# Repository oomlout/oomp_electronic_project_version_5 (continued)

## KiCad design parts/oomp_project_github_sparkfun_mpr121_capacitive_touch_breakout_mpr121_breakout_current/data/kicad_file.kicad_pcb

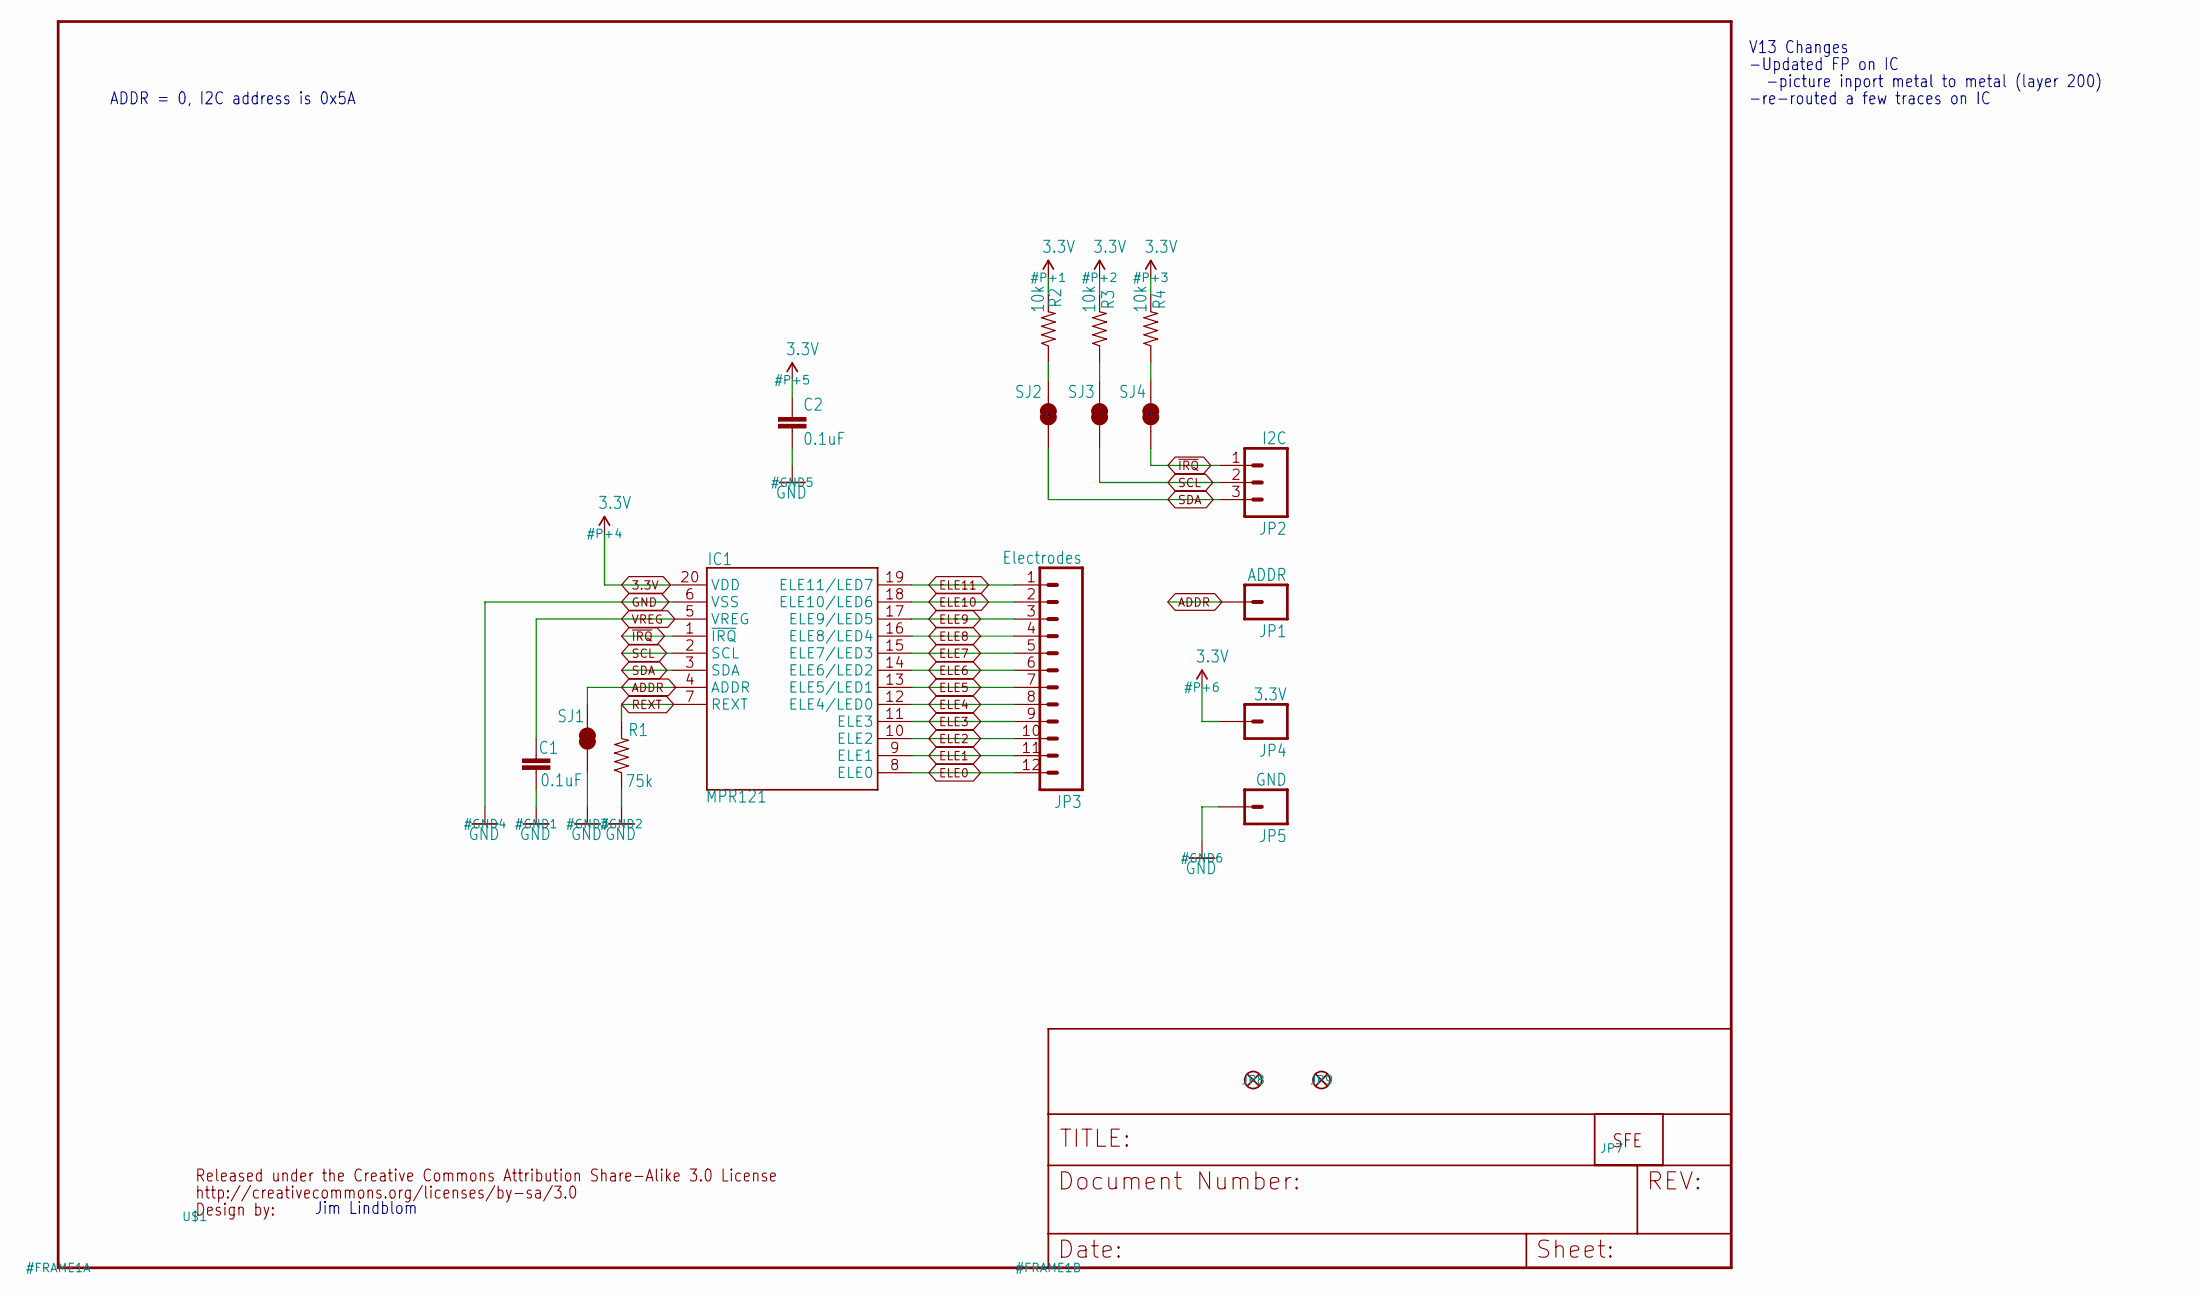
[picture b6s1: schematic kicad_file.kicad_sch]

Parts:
C1, C2: 0.1uF; 0603-CAP
IC1: MPR121; QFN-20-0.4MM-V2
JP1: ADDR; 1X01
JP2: I2C; 1X03
JP3: Electrodes; 1X12
JP4: 3.3V; 1X01
JP5: GND; 1X01
JP7: LOGO-SFENEW; SFE-NEW-WEBLOGO
JP8, JP9: FIDUCIAL1X2; FIDUCIAL-1X2
R1: 75k; 0603-RES
R2, R3, R4: 10k; 0603-RES
SJ1, SJ2, SJ3, SJ4: SOLDERJUMPERTRACE; SJ_2S-TRACE
U$1: CREATIVE_COMMONS

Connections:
3.3V: C2.1, IC1.20 (VDD), JP4.1, R2.2, R3.2, R4.2
ADDR: IC1.4 (ADDR), JP1.1, SJ1.2
ELE0: IC1.8 (ELE0), JP3.12
ELE1: IC1.9 (ELE1), JP3.11
ELE2: IC1.10 (ELE2), JP3.10
ELE3: IC1.11 (ELE3), JP3.9
ELE4: IC1.12 (ELE4/LED0), JP3.8
ELE5: IC1.13 (ELE5/LED1), JP3.7
ELE6: IC1.14 (ELE6/LED2), JP3.6
ELE7: IC1.15 (ELE7/LED3), JP3.5
ELE8: IC1.16 (ELE8/LED4), JP3.4
ELE9: IC1.17 (ELE9/LED5), JP3.3
ELE10: IC1.18 (ELE10/LED6), JP3.2
ELE11: IC1.19 (ELE11/LED7), JP3.1
GND: C1.2, C2.2, IC1.6 (VSS), JP5.1, R1.1, SJ1.1
REXT: IC1.7 (REXT), R1.2
SCL: IC1.2 (SCL), JP2.2, SJ3.1
SCL_PU: R3.1, SJ3.2
SDA: IC1.3 (SDA), JP2.3, SJ2.1
SDA_PU: R2.1, SJ2.2
VREG: C1.1, IC1.5 (VREG)
~IRQ_PU: R4.1, SJ4.2
~IRQ: IC1.1 (~IRQ), JP2.1, SJ4.1

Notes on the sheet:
-re-routed a few traces on IC
V13 Changes
Jim Lindblom
-Updated FP on IC
-picture inport metal to metal (layer 200)
ADDR = 0, I2C address is 0x5A

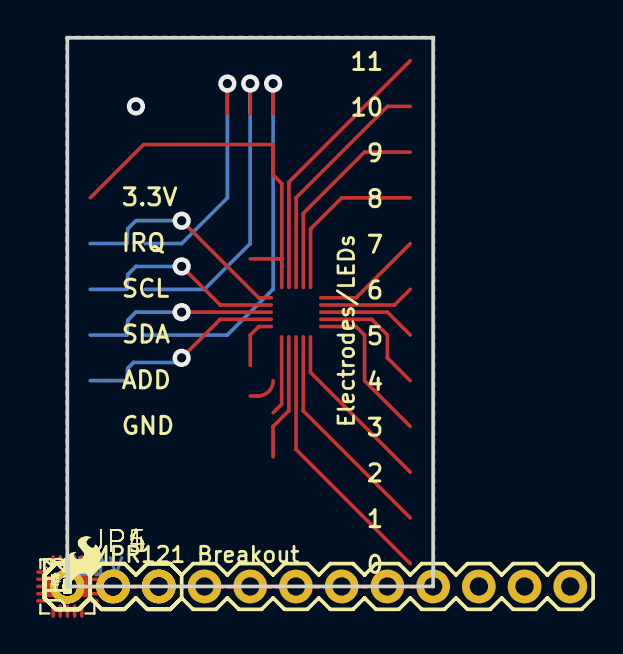
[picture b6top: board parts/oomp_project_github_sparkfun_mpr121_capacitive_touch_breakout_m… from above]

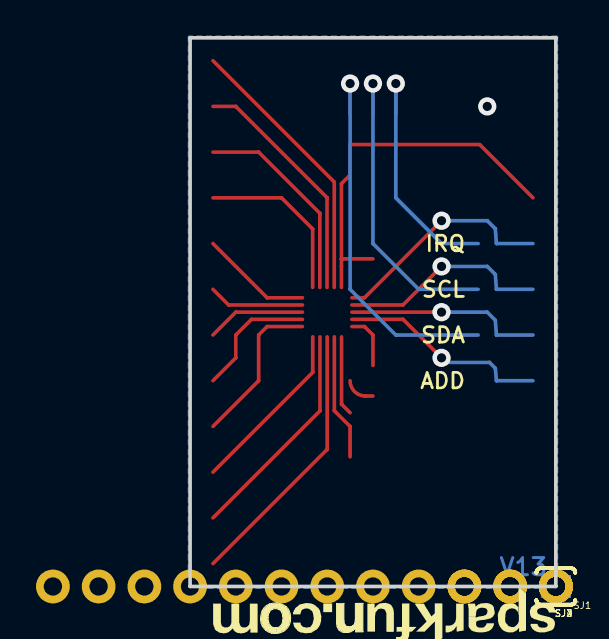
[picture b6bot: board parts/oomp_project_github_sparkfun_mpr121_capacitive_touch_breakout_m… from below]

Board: 2 copper layers, 20.3 x 30.5 mm, 21 parts (5 on the bottom side), 23 nets.

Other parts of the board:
JP6: LOGO-SFESK; SFE-LOGO-FLAME

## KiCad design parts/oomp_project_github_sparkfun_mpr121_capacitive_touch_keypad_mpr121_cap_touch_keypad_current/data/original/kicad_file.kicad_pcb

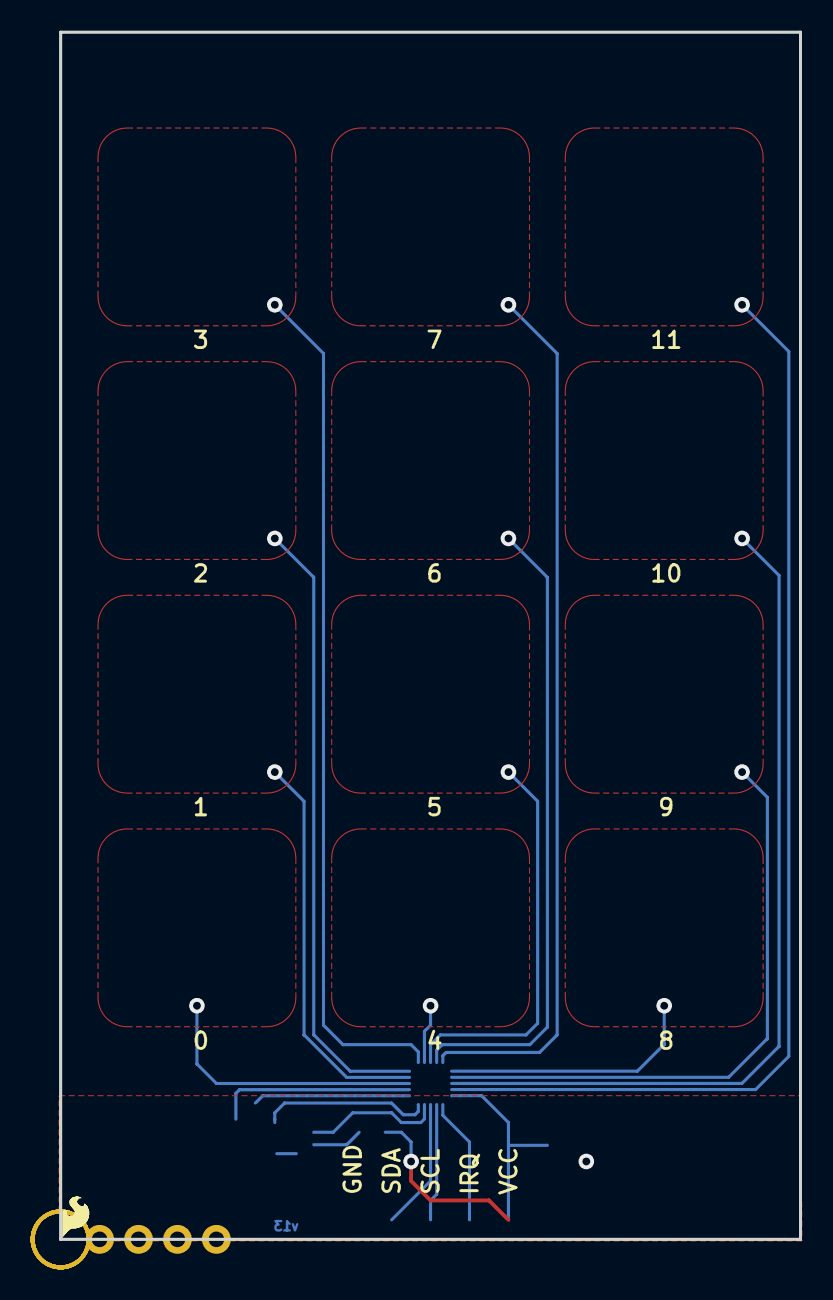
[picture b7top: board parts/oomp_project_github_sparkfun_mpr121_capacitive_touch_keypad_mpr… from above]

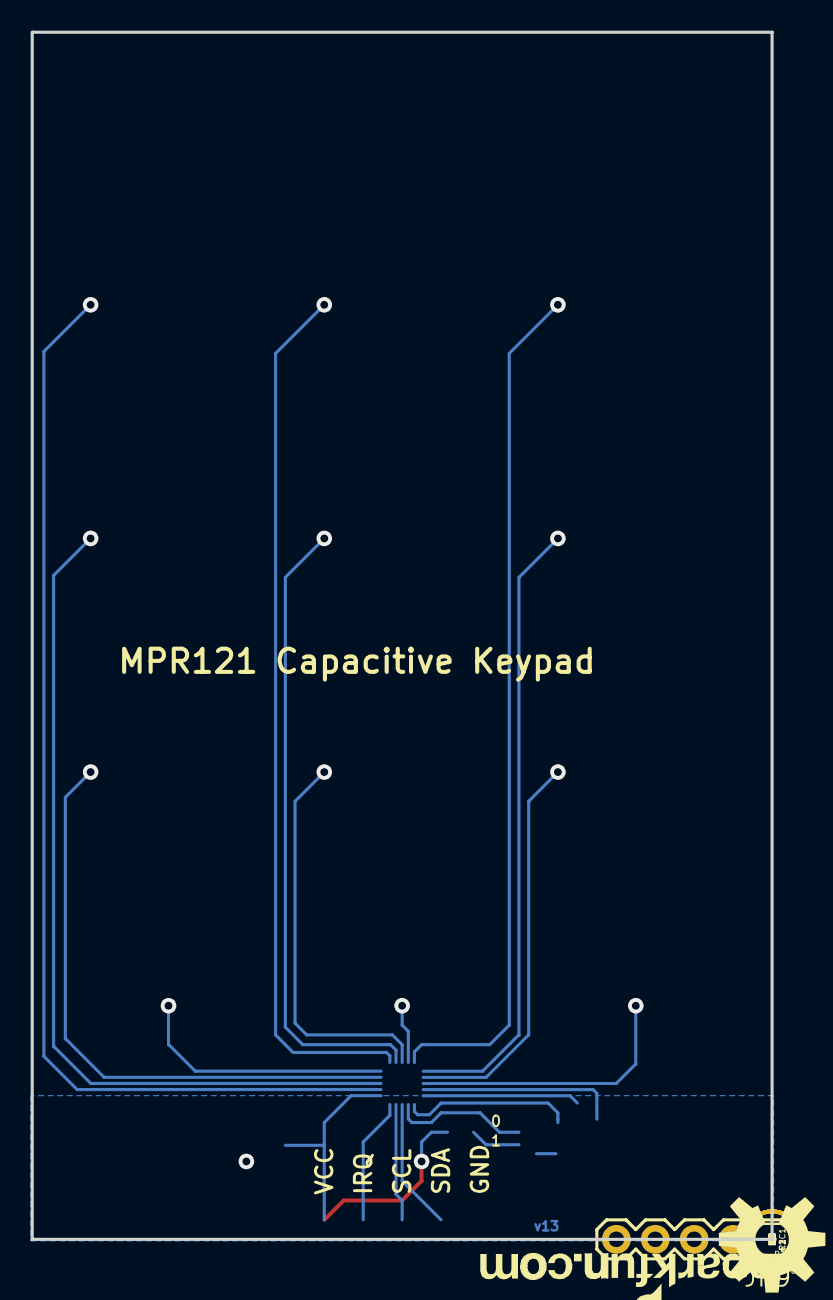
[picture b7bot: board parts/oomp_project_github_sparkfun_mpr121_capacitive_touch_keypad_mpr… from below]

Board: 2 copper layers, 48.3 x 78.7 mm, 19 parts (15 on the bottom side), 9 nets.

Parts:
C1, C2: 0.1uF; 0603-CAP
FRAME1: FRAME-LETTER; CREATIVE_COMMONS
IC1: MPR121; QFN-20-0.4MM-V2
JP1: LOGO-SFENEW; SFE-NEW-WEBLOGO
JP2, JP6: LOGO-SFESK; SFE-LOGO-FLAME
JP3, JP4, JP7, JP8: STAND-OFF
JP5, JP10: FIDUCIAL1X2; FIDUCIAL-1X2
JP9: 1X05
LOGO1: OSHW-LOGOL; OSHW-LOGO-L
R1: 75k; 0603-RES
R2: 10K; 0603-RES
SJ1: SJ_3_PASTE1&2
U$1: REVISION

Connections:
GND: C1.2, C2.2, IC1.6, JP9.1, R1.1, SJ1.1
unnamed: IC1.4, SJ1.2
unnamed: R2.1, SJ1.3
REXT: IC1.7, R1.2
SCL: IC1.2, JP9.3
SDA: IC1.3, JP9.2
VCC: C2.1, IC1.20, JP9.5, R2.2
VREG: C1.1, IC1.5
~IRQ: IC1.1, JP9.4

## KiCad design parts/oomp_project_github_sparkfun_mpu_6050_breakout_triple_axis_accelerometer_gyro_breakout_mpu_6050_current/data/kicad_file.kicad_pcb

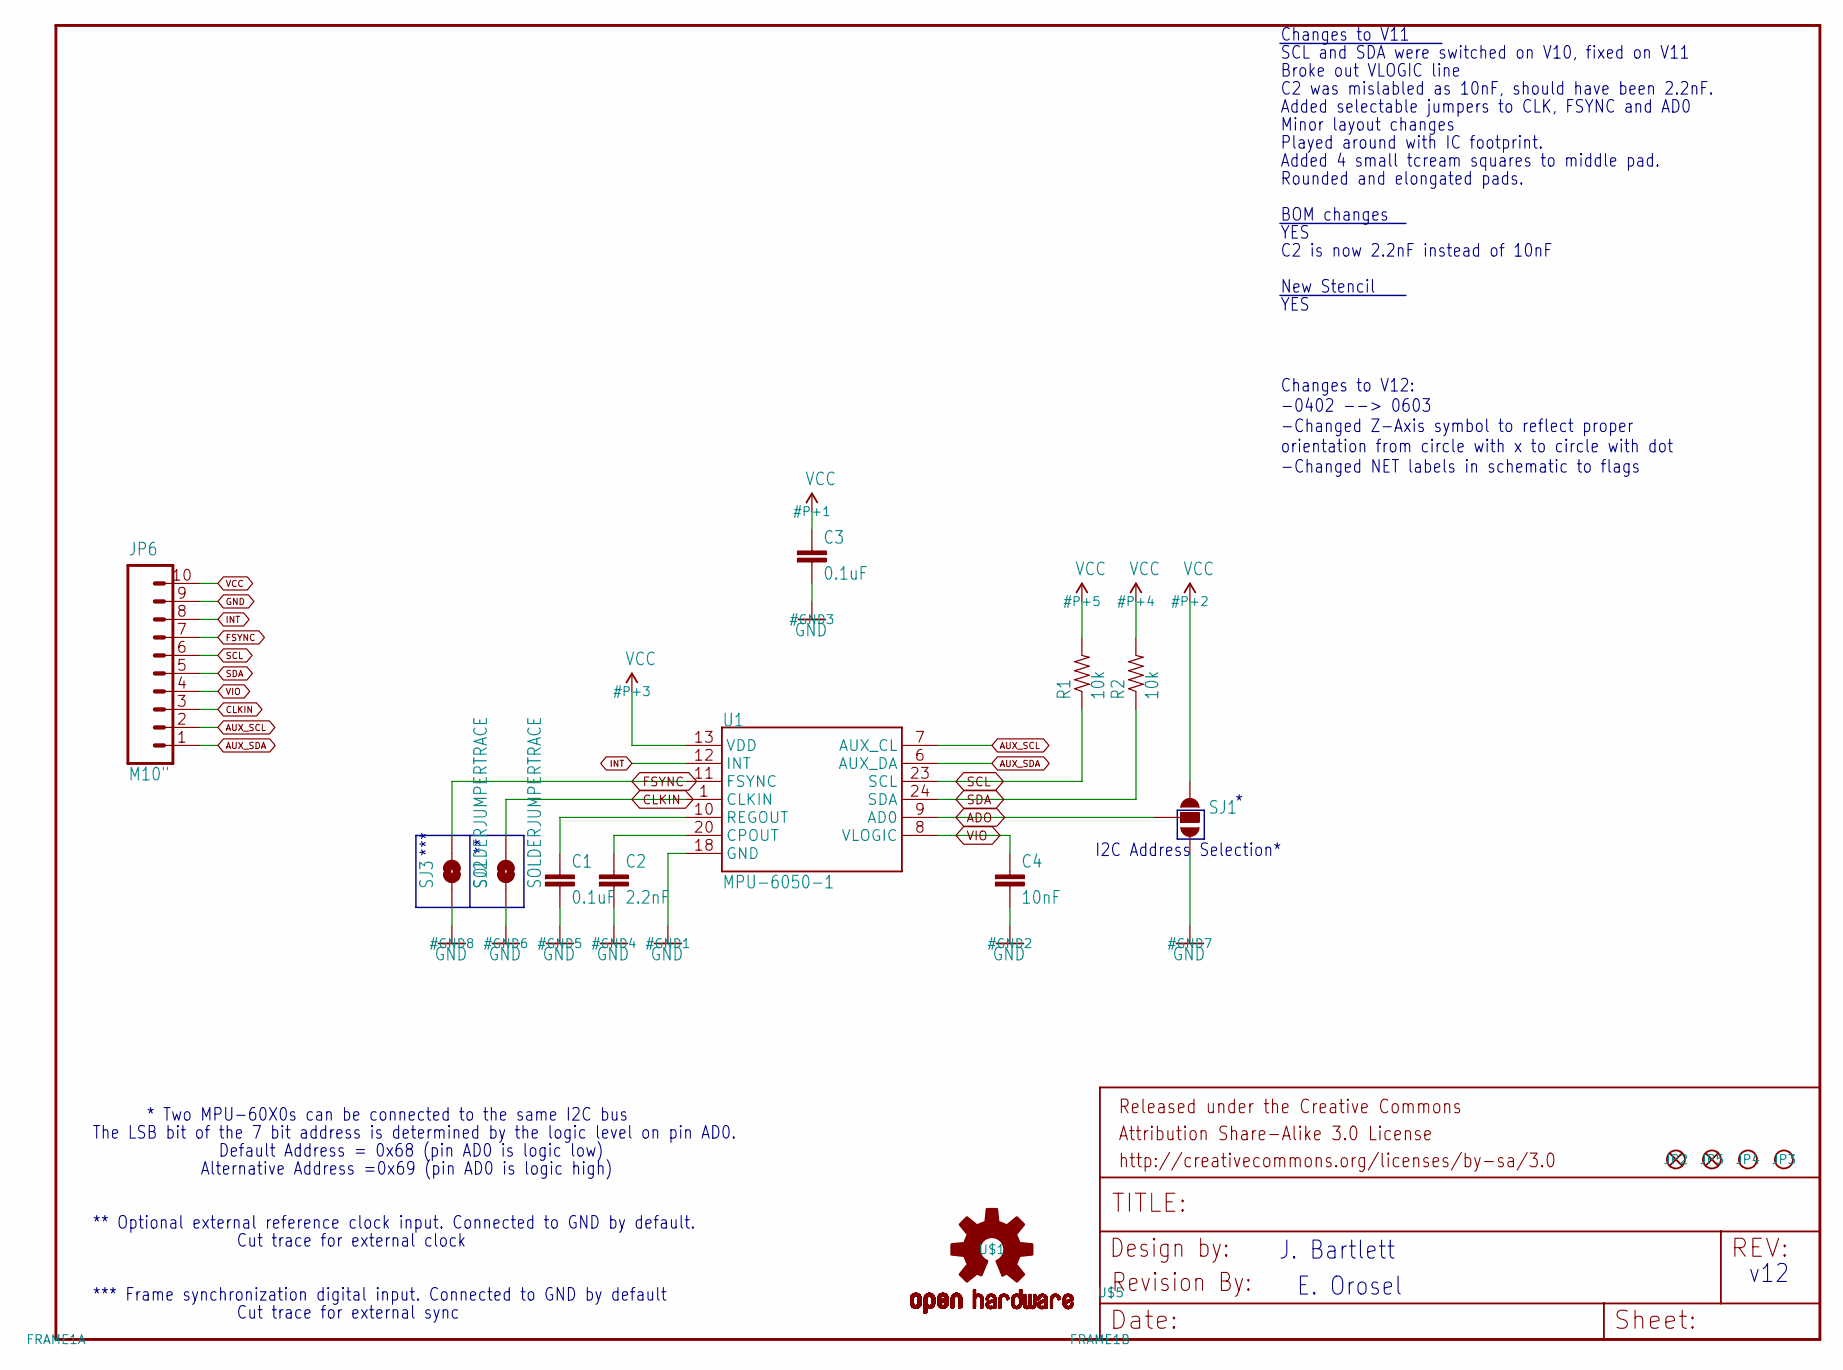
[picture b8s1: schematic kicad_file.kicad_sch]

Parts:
C1, C3: 0.1uF; 0603-CAP
C2: 2.2nF; 0603-CAP
C4: 10nF; 0603-CAP
FRAME1: FRAME-LETTER; CREATIVE_COMMONS
JP2, JP5: FIDUCIALUFIDUCIAL; MICRO-FIDUCIAL
JP3, JP4: STAND-OFFTIGHT; STAND-OFF-TIGHT
JP6: M10"; 1X10
R1, R2: 10k; 0603-RES
SJ1: SOLDERJUMPER_2WAYPASTE2&3; SJ_3_PASTE2&3
SJ2, SJ3: SOLDERJUMPERTRACE; SJ_2S-TRACE
U1: MPU-6050-1; QFN-24-4MM2
U$1: OSHW-LOGOS; OSHW-LOGO-S
U$5: REVISION

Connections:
ADO: SJ1.2, U1.9 (AD0)
AUX_SCL: JP6.2, U1.7 (AUX_CL)
AUX_SDA: JP6.1, U1.6 (AUX_DA)
CLKIN: JP6.3, SJ2.2, U1.1 (CLKIN)
FSYNC: JP6.7, SJ3.2, U1.11 (FSYNC)
GND: C1.2, C2.2, C3.2, C4.2, JP6.9, SJ1.3, SJ2.1, SJ3.1, U1.18 (GND)
INT: JP6.8, U1.12 (INT)
unnamed: C2.1, U1.20 (CPOUT)
unnamed: C1.1, U1.10 (REGOUT)
SCL: JP6.6, R1.1, U1.23 (SCL)
SDA: JP6.5, R2.1, U1.24 (SDA)
VCC: C3.1, JP6.10, R1.2, R2.2, SJ1.1, U1.13 (VDD)
VIO: C4.1, JP6.4, U1.8 (VLOGIC)

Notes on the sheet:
YES
New Stencil
Alternative Address =0x69 (pin AD0 is logic high)
I2C Address Selection*
***
* Two MPU-60X0s can be connected to the same I2C bus
E. Orosel
Default Address = 0x68 (pin AD0 is logic low)
BOM changes
Cut trace for external clock
Cut trace for external sync
SCL and SDA were switched on V10, fixed on V11
** Optional external reference clock input. Connected to GND by default.
v12
Played around with IC footprint.
C2 was mislabled as 10nF, should have been 2.2nF.
Rounded and elongated pads.
Broke out VLOGIC line
Changes to V12: -0402 --> 0603 -Changed Z-Axis symbol to reflect proper orientation from circle with x to circle with dot -Changed NET labels in schematic to flags
Changes to V11
J. Bartlett
*** Frame synchronization digital input. Connected to GND by default
Added 4 small tcream squares to middle pad.
The LSB bit of the 7 bit address is determined by the logic level on pin AD0.
Minor layout changes
Added selectable jumpers to CLK, FSYNC and AD0
C2 is now 2.2nF instead of 10nF

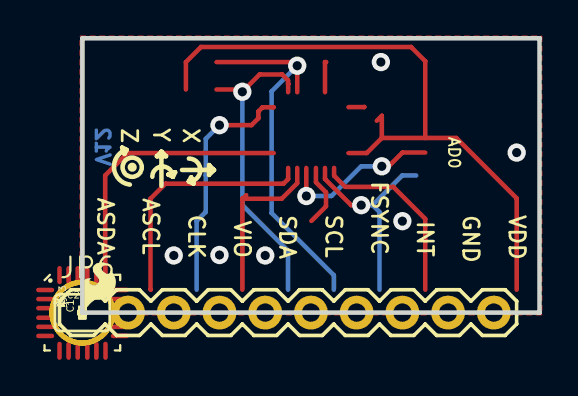
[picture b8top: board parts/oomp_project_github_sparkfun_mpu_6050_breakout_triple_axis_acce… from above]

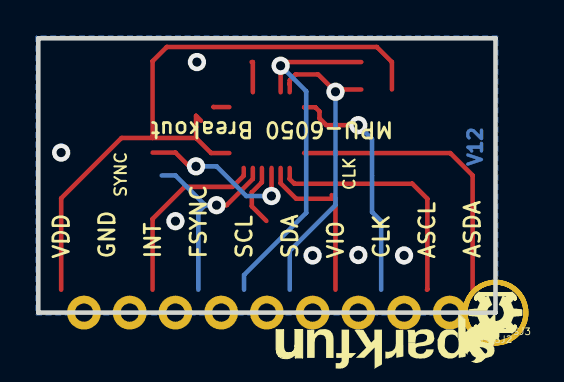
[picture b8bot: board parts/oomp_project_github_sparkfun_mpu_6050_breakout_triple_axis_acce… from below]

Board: 2 copper layers, 25.4 x 15.2 mm, 21 parts (5 on the bottom side), 13 nets.

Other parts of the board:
U$2, U$3: SFE-LOGO-FLAME
U$4: SFE-NEW-WEB
